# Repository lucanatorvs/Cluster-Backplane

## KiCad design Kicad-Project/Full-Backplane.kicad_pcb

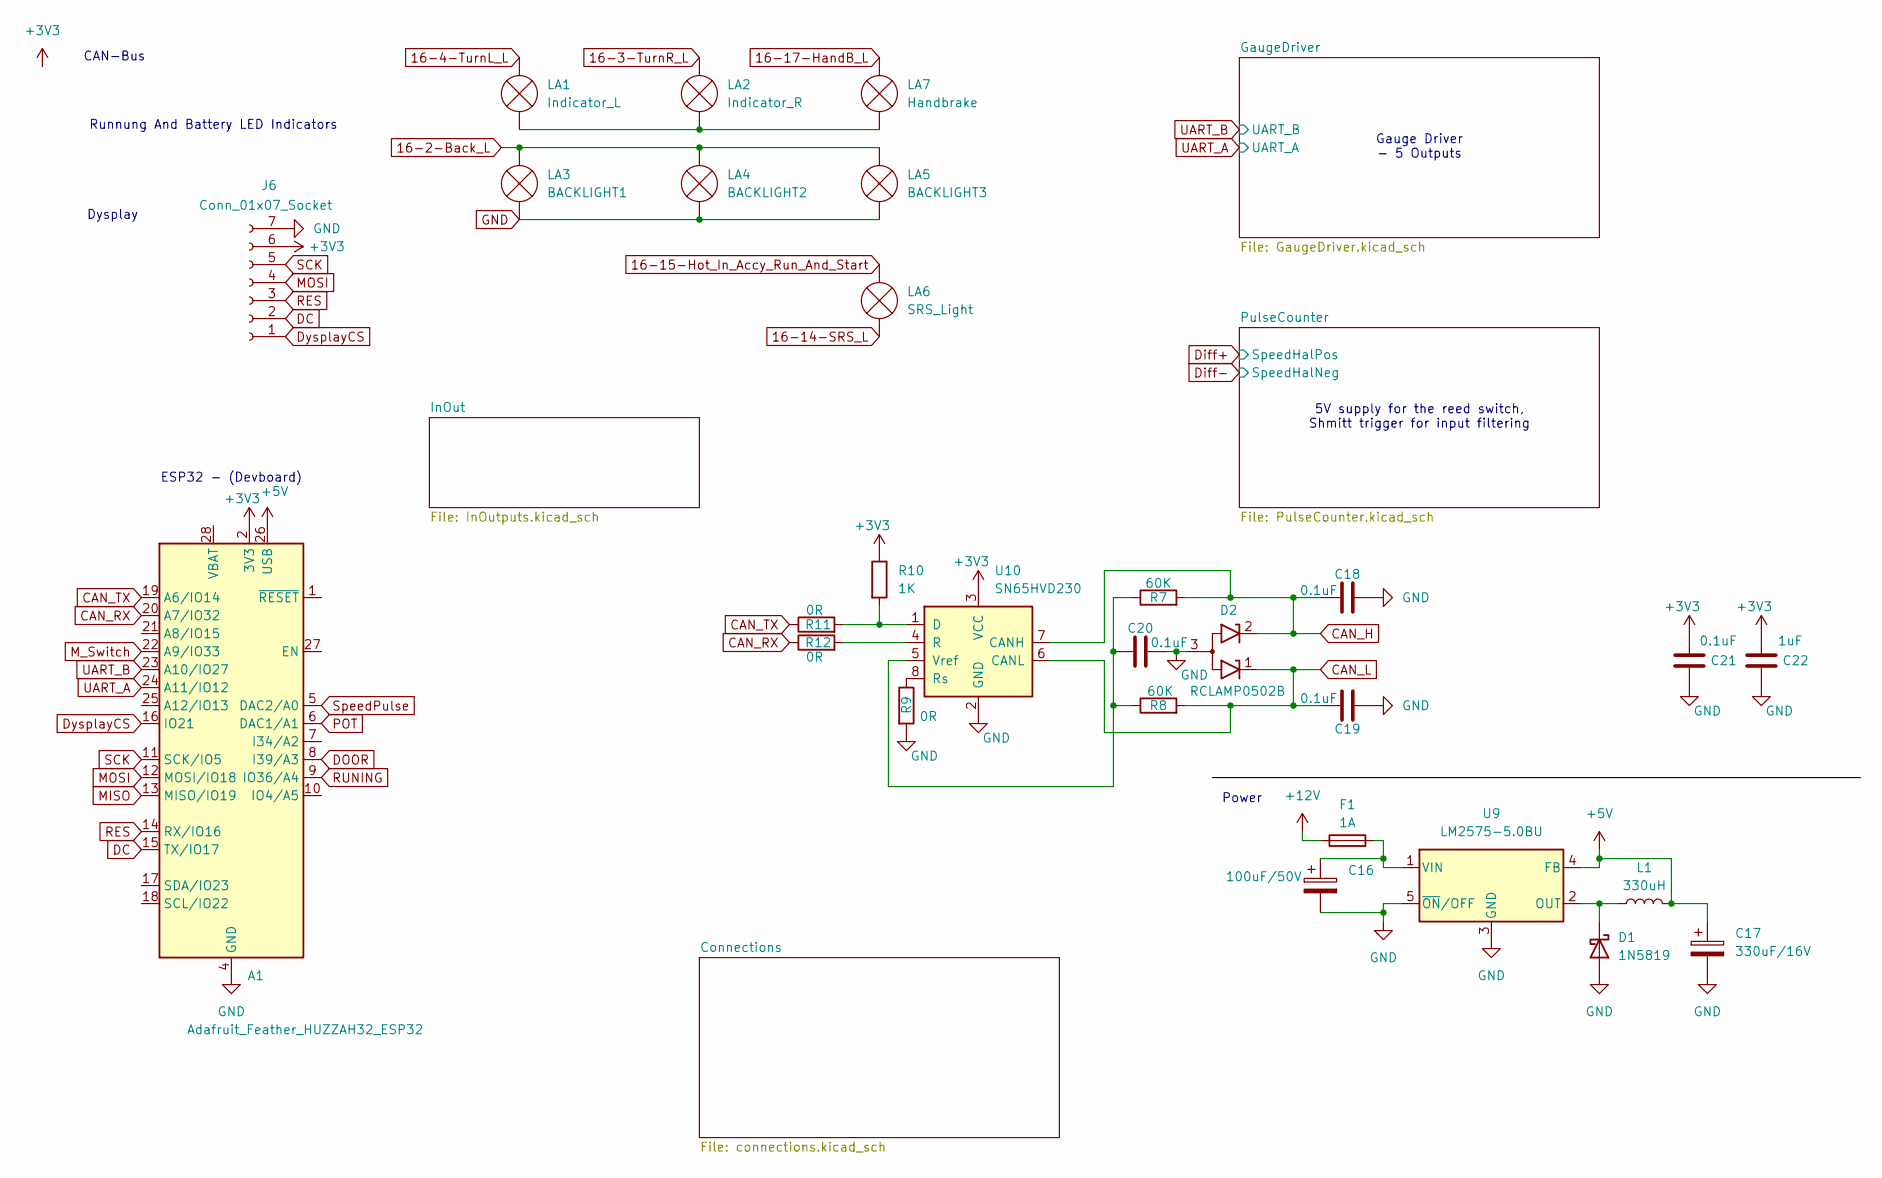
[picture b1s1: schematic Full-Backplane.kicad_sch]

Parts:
A1: Adafruit_Feather_HUZZAH32_ESP32; Adafruit_Feather
C16: 100uF/50V; CP_Radial_D8.0mm_P3.50mm
C17: 330uF/16V; CP_Radial_D8.0mm_P3.50mm
C18, C19, C20, C21: 0.1uF; C_0805_2012Metric_Pad1.18x1.45mm_HandSolder
C22: 1uF; C_0805_2012Metric_Pad1.18x1.45mm_HandSolder
D1: 1N5819; D_DO-41_SOD81_P10.16mm_Horizontal
D2: RCLAMP0502B; SOT-416
F1: 1A; Fuse_0402_1005Metric_Pad0.77x0.64mm_HandSolder
J6: Conn_01x07_Socket; PinHeader_1x07_P2.54mm_Vertical
L1: 330uH; L_Radial_D9.5mm_P5.00mm_Fastron_07HVP
LA1: Indicator_L; Smallight
LA2: Indicator_R; Smallight
LA3: BACKLIGHT1; Biglight
LA4: BACKLIGHT2; Biglight
LA5: BACKLIGHT3; Biglight
LA6: SRS_Light; Smallight
LA7: Handbrake; Smallight
R7, R8: 60K; R_0805_2012Metric_Pad1.20x1.40mm_HandSolder
R9, R11, R12: 0R; R_0805_2012Metric_Pad1.20x1.40mm_HandSolder
R10: 1K; R_0805_2012Metric_Pad1.20x1.40mm_HandSolder
U9: LM2575-5.0BU; TO-263-5_TabPin3
U10: SN65HVD230; SOIC-8_3.9x4.9mm_P1.27mm

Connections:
16-2-Back_L: LA3.2 (+), LA4.2 (+), LA5.2 (+); also elsewhere on the board
16-3-TurnR_L: LA2.2 (+); also elsewhere on the board
16-4-TurnL_L: LA1.2 (+); also elsewhere on the board
16-14-SRS_L: LA6.1 (-); also elsewhere on the board
16-15-Hot_In_Accy_Run_And_Start: LA6.2 (+); also elsewhere on the board
16-17-HandB_L: LA7.2 (+); also elsewhere on the board
+3V3: A1.2 (3V3), C21.1, C22.1, J6.6, R10.1, U10.3 (VCC); also elsewhere on the board
+5V: A1.26 (USB), C17.1, L1.2, U9.4 (FB); also elsewhere on the board
+12V: F1.1
CAN_H: C18.1, D2.2 (K2), R7.2, U10.7 (CANH); also elsewhere on the board
CAN_L: C19.1, D2.1 (K1), R8.2, U10.6 (CANL); also elsewhere on the board
CAN_RX: A1.20 (A7/IO32), R12.1
CAN_TX: A1.19 (A6/IO14), R11.1
DC: A1.15 (TX/IO17), J6.2
DOOR: A1.8 (I39/A3)
DysplayCS: A1.16 (IO21), J6.1
GND: A1.4 (GND), C16.2, C17.2, C18.2, C19.2, C20.2, C21.2, C22.2, D1.2 (A), D2.3 (A), J6.7, LA3.1 (-), LA4.1 (-), LA5.1 (-), R9.2, U9.3 (GND), U9.5 (~ON/OFF), U10.2 (GND); also elsewhere on the board
MISO: A1.13 (MISO/IO19)
MOSI: A1.12 (MOSI/IO18), J6.4
M_Switch: A1.22 (A9/IO33)
unnamed: D1.1 (K), L1.1, U9.2 (OUT)
unnamed: LA1.1 (-), LA2.1 (-), LA7.1 (-)
unnamed: C16.1, F1.2, U9.1 (VIN)
unnamed: R10.2, R11.2, U10.1 (D)
unnamed: R12.2, U10.4 (R)
unnamed: R9.1, U10.8 (Rs)
unnamed: C20.1, R7.1, R8.1, U10.5 (Vref)
POT: A1.6 (DAC1/A1)
RES: A1.14 (RX/IO16), J6.3
RUNING: A1.9 (IO36/A4)
SCK: A1.11 (SCK/IO5), J6.5
SpeedPulse: A1.5 (DAC2/A0); also elsewhere on the board
UART_A: A1.24 (A11/IO12); also elsewhere on the board
UART_B: A1.23 (A10/IO27); also elsewhere on the board

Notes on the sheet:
Gauge Driver - 5 Outputs
5V supply for the reed switch, Shmitt trigger for input filtering
CAN-Bus
Dysplay
Runnung And Battery LED Indicators
Power
ESP32 - (Devboard)

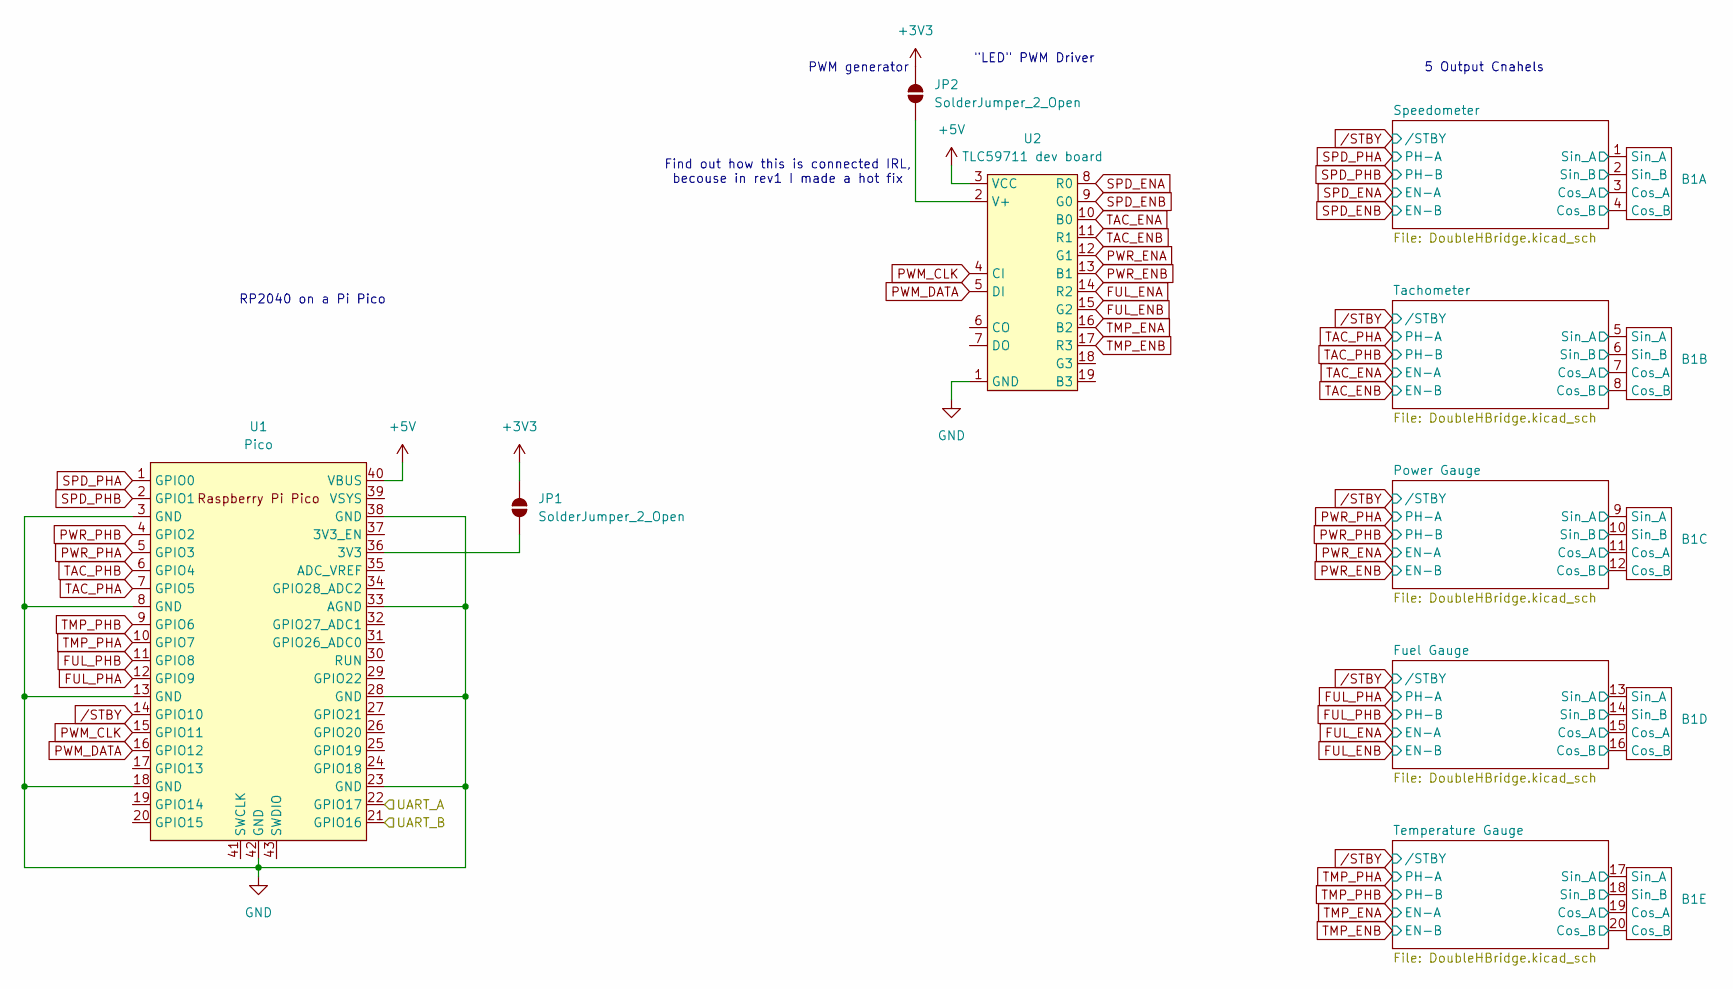
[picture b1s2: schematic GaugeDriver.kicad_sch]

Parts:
B1: Backplane
JP1, JP2: SolderJumper_2_Open; SolderJumper-2_P1.3mm_Open_TrianglePad1.0x1.5mm
U1: Pico; RPi_Pico_SMD_TH
U2: TLC59711 dev board; Adafruit TLC59711

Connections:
+3V3: JP1.2 (B), JP2.2 (B); also elsewhere on the board
+5V: U1.40 (VBUS), U2.3 (VCC); also elsewhere on the board
/GaugeDriver/Fuel Gauge/Cos_A: B1.15 (Cos_A); also elsewhere on the board
/GaugeDriver/Fuel Gauge/Cos_B: B1.16 (Cos_B); also elsewhere on the board
/GaugeDriver/Fuel Gauge/Sin_A: B1.13 (Sin_A); also elsewhere on the board
/GaugeDriver/Fuel Gauge/Sin_B: B1.14 (Sin_B); also elsewhere on the board
/GaugeDriver/Power Gauge/Cos_A: B1.11 (Cos_A); also elsewhere on the board
/GaugeDriver/Power Gauge/Cos_B: B1.12 (Cos_B); also elsewhere on the board
/GaugeDriver/Power Gauge/Sin_A: B1.9 (Sin_A); also elsewhere on the board
/GaugeDriver/Power Gauge/Sin_B: B1.10 (Sin_B); also elsewhere on the board
/GaugeDriver/Speedometer/Cos_A: B1.3 (Cos_A); also elsewhere on the board
/GaugeDriver/Speedometer/Cos_B: B1.4 (Cos_B); also elsewhere on the board
/GaugeDriver/Speedometer/Sin_A: B1.1 (Sin_A); also elsewhere on the board
/GaugeDriver/Speedometer/Sin_B: B1.2 (Sin_B); also elsewhere on the board
/GaugeDriver/Tachometer/Cos_A: B1.7 (Cos_A); also elsewhere on the board
/GaugeDriver/Tachometer/Cos_B: B1.8 (Cos_B); also elsewhere on the board
/GaugeDriver/Tachometer/Sin_A: B1.5 (Sin_A); also elsewhere on the board
/GaugeDriver/Tachometer/Sin_B: B1.6 (Sin_B); also elsewhere on the board
/GaugeDriver/Temperature Gauge/Cos_A: B1.19 (Cos_A); also elsewhere on the board
/GaugeDriver/Temperature Gauge/Cos_B: B1.20 (Cos_B); also elsewhere on the board
/GaugeDriver/Temperature Gauge/Sin_A: B1.17 (Sin_A); also elsewhere on the board
/GaugeDriver/Temperature Gauge/Sin_B: B1.18 (Sin_B); also elsewhere on the board
FUL_ENA: U2.14 (R2); also elsewhere on the board
FUL_ENB: U2.15 (G2); also elsewhere on the board
FUL_PHA: U1.12 (GPIO9); also elsewhere on the board
FUL_PHB: U1.11 (GPIO8); also elsewhere on the board
GND: U1.3 (GND), U1.8 (GND), U1.13 (GND), U1.18 (GND), U1.23 (GND), U1.28 (GND), U1.33 (AGND), U1.38 (GND), U1.42 (GND), U2.1 (GND); also elsewhere on the board
unnamed: JP1.1 (A), U1.36 (3V3)
unnamed: JP2.1 (A), U2.2 (V+)
PWM_CLK: U1.15 (GPIO11), U2.4 (CI)
PWM_DATA: U1.16 (GPIO12), U2.5 (DI)
PWR_ENA: U2.12 (G1); also elsewhere on the board
PWR_ENB: U2.13 (B1); also elsewhere on the board
PWR_PHA: U1.5 (GPIO3); also elsewhere on the board
PWR_PHB: U1.4 (GPIO2); also elsewhere on the board
SPD_ENA: U2.8 (R0); also elsewhere on the board
SPD_ENB: U2.9 (G0); also elsewhere on the board
SPD_PHA: U1.1 (GPIO0); also elsewhere on the board
SPD_PHB: U1.2 (GPIO1); also elsewhere on the board
TAC_ENA: U2.10 (B0); also elsewhere on the board
TAC_ENB: U2.11 (R1); also elsewhere on the board
TAC_PHA: U1.7 (GPIO5); also elsewhere on the board
TAC_PHB: U1.6 (GPIO4); also elsewhere on the board
TMP_ENA: U2.16 (B2); also elsewhere on the board
TMP_ENB: U2.17 (R3); also elsewhere on the board
TMP_PHA: U1.10 (GPIO7); also elsewhere on the board
TMP_PHB: U1.9 (GPIO6); also elsewhere on the board
UART_A: U1.22 (GPIO17); also elsewhere on the board
UART_B: U1.21 (GPIO16); also elsewhere on the board
/STBY: U1.14 (GPIO10); also elsewhere on the board

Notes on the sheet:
RP2040 on a Pi Pico
Find out how this is connected IRL, becouse in rev1 I made a hot fix
5 Output Cnahels
"LED" PWM Driver
PWM generator

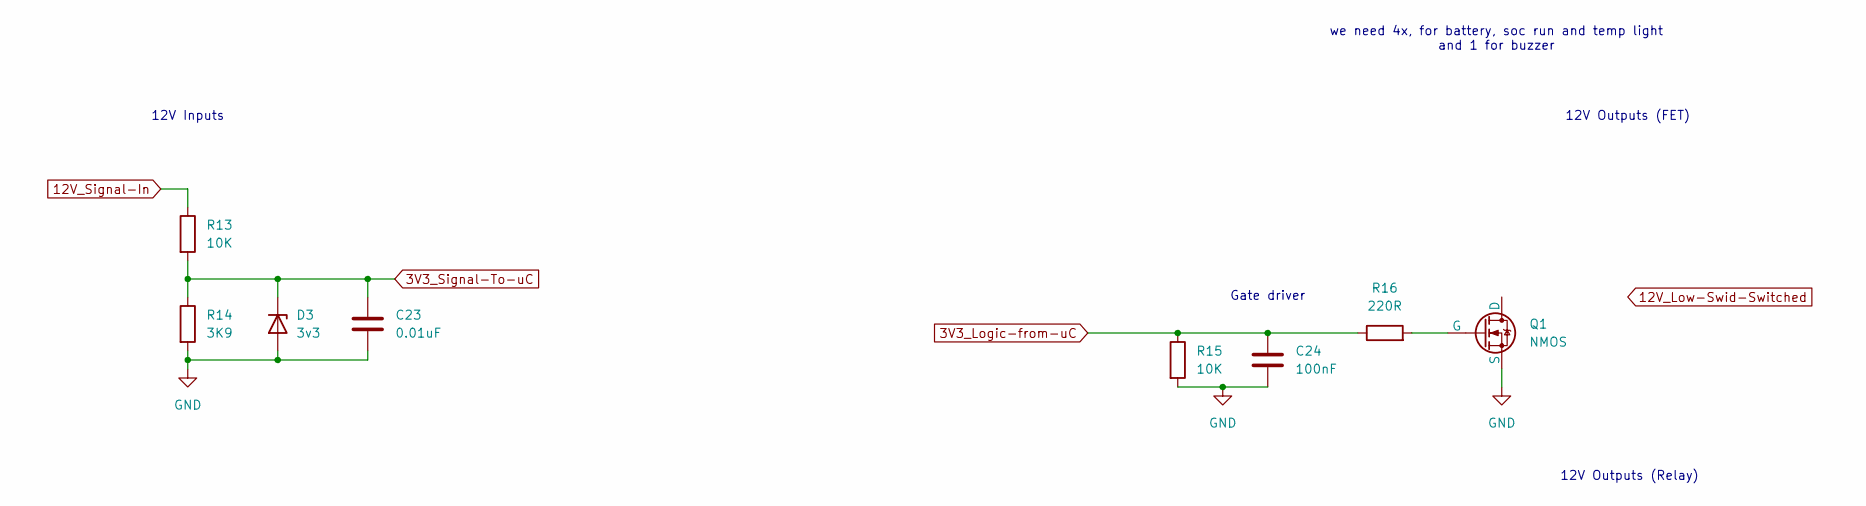
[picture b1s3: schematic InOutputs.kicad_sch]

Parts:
C23: 0.01uF; C_0805_2012Metric_Pad1.18x1.45mm_HandSolder
C24: 100nF
D3: 3v3; D_MiniMELF_Handsoldering
Q1: NMOS; IRFH9714
R13: 10K; R_0805_2012Metric_Pad1.20x1.40mm_HandSolder
R14: 3K9; R_0805_2012Metric_Pad1.20x1.40mm_HandSolder
R15: 10K
R16: 220R

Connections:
3V3_Logic-from-uC: Q1.2 (G), R16.2
3V3_Signal-To-uC: C23.1, D3.1 (K), R13.2, R14.1
12V_Low-Swid-Switched: Q1.1 (D)
12V_Signal-In: R13.1
GND: C23.2, C24.2, D3.2 (A), Q1.3 (S), R14.2, R15.2; also elsewhere on the board
unnamed: C24.1, R15.1, R16.1

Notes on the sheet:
Gate driver
12V Inputs
12V Outputs (Relay)
12V Outputs (FET)
we need 4x, for battery, soc run and temp light and 1 for buzzer

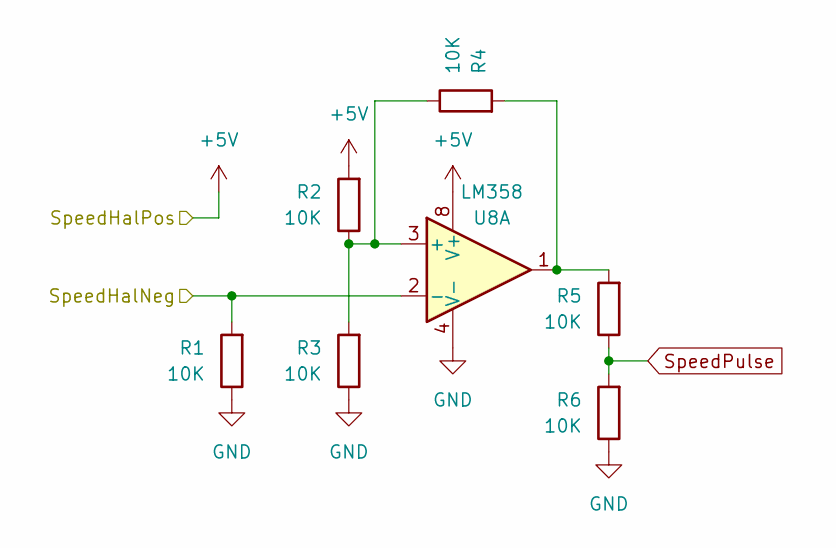
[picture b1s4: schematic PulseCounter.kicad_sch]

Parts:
R1, R2, R3, R4, R5, R6: 10K; R_0805_2012Metric_Pad1.20x1.40mm_HandSolder
U8: LM358; SSOP-8_5.25x5.24mm_P1.27mm

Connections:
Diff+: R2.2, U8.8 (V+); also elsewhere on the board
Diff-: R1.2, U8.2 (-); also elsewhere on the board
GND: R1.1, R3.1, R6.1, U8.4 (V-); also elsewhere on the board
unnamed: R4.2, R5.2, U8.1
unnamed: R2.1, R3.2, R4.1, U8.3 (+)
SpeedPulse: R5.1, R6.2; also elsewhere on the board

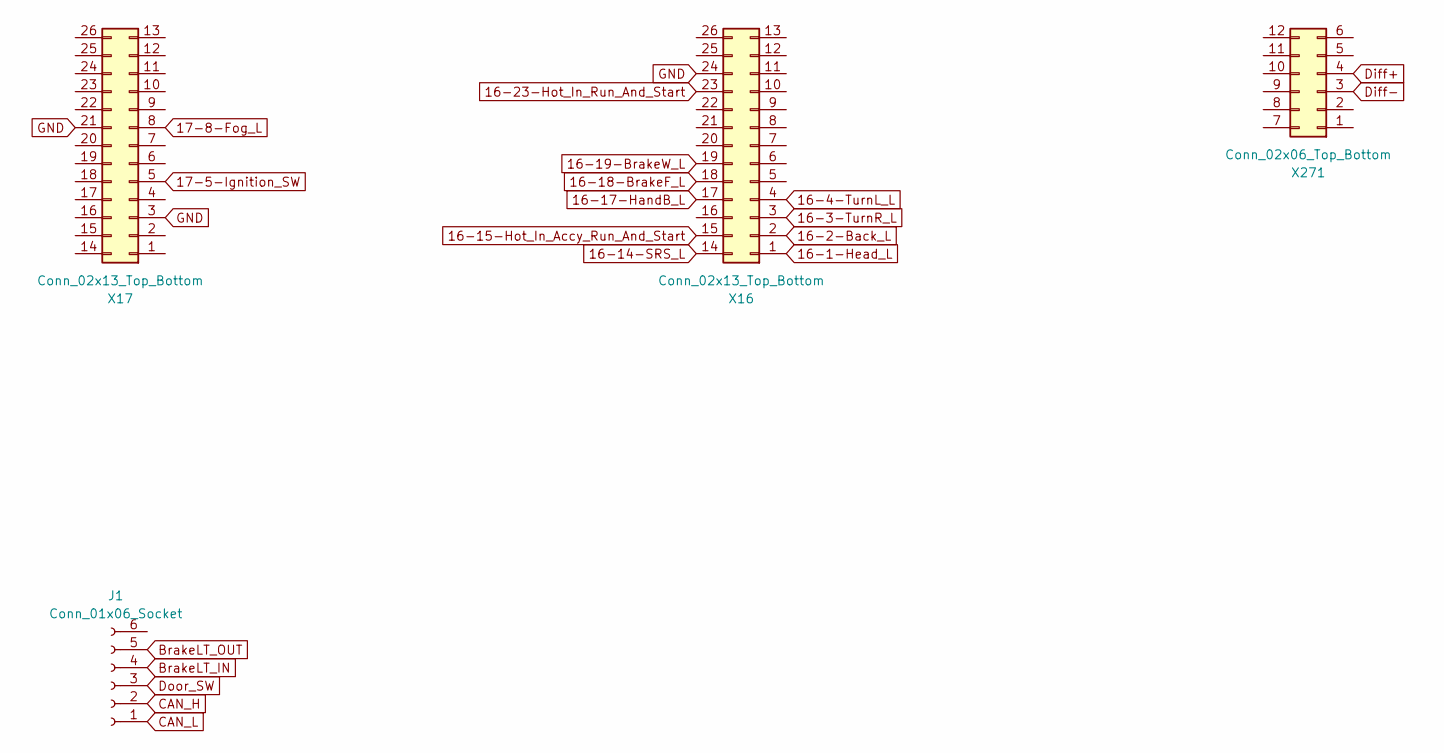
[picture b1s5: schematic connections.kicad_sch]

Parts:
J1: Conn_01x06_Socket; PinHeader_2x03_P2.54mm_Vertical
X16, X17: Conn_02x13_Top_Bottom; PinHeader_2x13_P2.54mm_Vertical
X271: Conn_02x06_Top_Bottom; PinHeader_2x06_P2.54mm_Vertical

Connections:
16-1-Head_L: X16.1
16-2-Back_L: X16.2; also elsewhere on the board
16-3-TurnR_L: X16.3; also elsewhere on the board
16-4-TurnL_L: X16.4; also elsewhere on the board
16-14-SRS_L: X16.14; also elsewhere on the board
16-15-Hot_In_Accy_Run_And_Start: X16.15; also elsewhere on the board
16-17-HandB_L: X16.17; also elsewhere on the board
16-18-BrakeF_L: X16.18
16-19-BrakeW_L: X16.19
16-23-Hot_In_Run_And_Start: X16.23
17-5-Ignition_SW: X17.5
17-8-Fog_L: X17.8
BrakeLT_IN: J1.4
BrakeLT_OUT: J1.5
CAN_H: J1.2; also elsewhere on the board
CAN_L: J1.1; also elsewhere on the board
Diff+: X271.4; also elsewhere on the board
Diff-: X271.3; also elsewhere on the board
Door_SW: J1.3
GND: X16.24, X17.3, X17.21; also elsewhere on the board

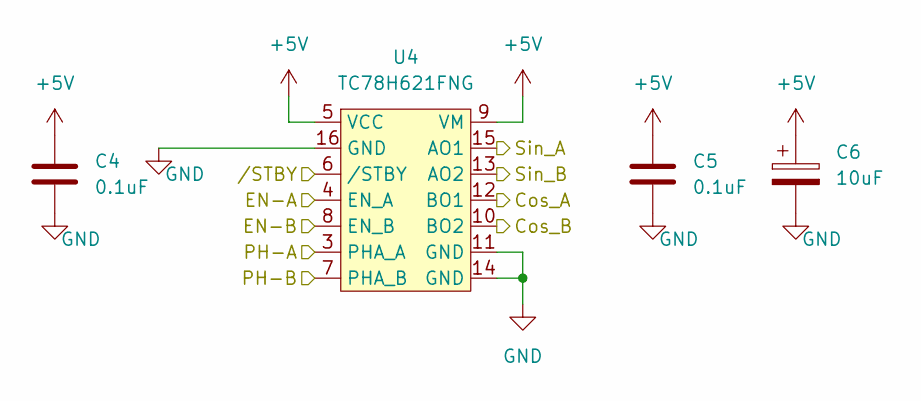
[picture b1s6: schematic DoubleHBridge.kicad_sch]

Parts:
C4, C5: 0.1uF; C_0805_2012Metric
C6: 10uF; CP_Elec_5x5.4
U4: TC78H621FNG; TSSOP-16_4.4x5mm_P0.65mm

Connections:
+5V: C4.1, C5.1, C6.1, U4.5 (VCC), U4.9 (VM); also elsewhere on the board
/GaugeDriver/Speedometer/Cos_A: U4.12 (BO1); also elsewhere on the board
/GaugeDriver/Speedometer/Cos_B: U4.10 (BO2); also elsewhere on the board
/GaugeDriver/Speedometer/Sin_A: U4.15 (AO1); also elsewhere on the board
/GaugeDriver/Speedometer/Sin_B: U4.13 (AO2); also elsewhere on the board
GND: C4.2, C5.2, C6.2, U4.11 (GND), U4.14 (GND), U4.16 (GND); also elsewhere on the board
SPD_ENA: U4.4 (EN_A); also elsewhere on the board
SPD_ENB: U4.8 (EN_B); also elsewhere on the board
SPD_PHA: U4.3 (PHA_A); also elsewhere on the board
SPD_PHB: U4.7 (PHA_B); also elsewhere on the board
/STBY: U4.6 (/STBY); also elsewhere on the board

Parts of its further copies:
C1, C2, C7, C8, C10, C11, C13, C14: 0.1uF; C_0805_2012Metric
C3, C9, C12, C15: 10uF; CP_Elec_5x5.4
U3, U5, U6, U7: TC78H621FNG; TSSOP-16_4.4x5mm_P0.65mm

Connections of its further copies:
+5V: C1.1, C2.1, C3.1, C7.1, C8.1, C9.1, C10.1, C11.1, C12.1, C13.1, C14.1, C15.1, U3.5 (VCC), U3.9 (VM), U5.5 (VCC), U5.9 (VM), U6.5 (VCC), U6.9 (VM), U7.5 (VCC), U7.9 (VM); also elsewhere on the board
/GaugeDriver/Fuel Gauge/Cos_A: U6.12 (BO1); also elsewhere on the board
/GaugeDriver/Fuel Gauge/Cos_B: U6.10 (BO2); also elsewhere on the board
/GaugeDriver/Fuel Gauge/Sin_A: U6.15 (AO1); also elsewhere on the board
/GaugeDriver/Fuel Gauge/Sin_B: U6.13 (AO2); also elsewhere on the board
/GaugeDriver/Power Gauge/Cos_A: U5.12 (BO1); also elsewhere on the board
/GaugeDriver/Power Gauge/Cos_B: U5.10 (BO2); also elsewhere on the board
/GaugeDriver/Power Gauge/Sin_A: U5.15 (AO1); also elsewhere on the board
/GaugeDriver/Power Gauge/Sin_B: U5.13 (AO2); also elsewhere on the board
/GaugeDriver/Tachometer/Cos_A: U3.12 (BO1); also elsewhere on the board
/GaugeDriver/Tachometer/Cos_B: U3.10 (BO2); also elsewhere on the board
/GaugeDriver/Tachometer/Sin_A: U3.15 (AO1); also elsewhere on the board
/GaugeDriver/Tachometer/Sin_B: U3.13 (AO2); also elsewhere on the board
/GaugeDriver/Temperature Gauge/Cos_A: U7.12 (BO1); also elsewhere on the board
/GaugeDriver/Temperature Gauge/Cos_B: U7.10 (BO2); also elsewhere on the board
/GaugeDriver/Temperature Gauge/Sin_A: U7.15 (AO1); also elsewhere on the board
/GaugeDriver/Temperature Gauge/Sin_B: U7.13 (AO2); also elsewhere on the board
FUL_ENA: U6.4 (EN_A); also elsewhere on the board
FUL_ENB: U6.8 (EN_B); also elsewhere on the board
FUL_PHA: U6.3 (PHA_A); also elsewhere on the board
FUL_PHB: U6.7 (PHA_B); also elsewhere on the board
GND: C1.2, C2.2, C3.2, C7.2, C8.2, C9.2, C10.2, C11.2, C12.2, C13.2, C14.2, C15.2, U3.11 (GND), U3.14 (GND), U3.16 (GND), U5.11 (GND), U5.14 (GND), U5.16 (GND), U6.11 (GND), U6.14 (GND), U6.16 (GND), U7.11 (GND), U7.14 (GND), U7.16 (GND); also elsewhere on the board
PWR_ENA: U5.4 (EN_A); also elsewhere on the board
PWR_ENB: U5.8 (EN_B); also elsewhere on the board
PWR_PHA: U5.3 (PHA_A); also elsewhere on the board
PWR_PHB: U5.7 (PHA_B); also elsewhere on the board
TAC_ENA: U3.4 (EN_A); also elsewhere on the board
TAC_ENB: U3.8 (EN_B); also elsewhere on the board
TAC_PHA: U3.3 (PHA_A); also elsewhere on the board
TAC_PHB: U3.7 (PHA_B); also elsewhere on the board
TMP_ENA: U7.4 (EN_A); also elsewhere on the board
TMP_ENB: U7.8 (EN_B); also elsewhere on the board
TMP_PHA: U7.3 (PHA_A); also elsewhere on the board
TMP_PHB: U7.7 (PHA_B); also elsewhere on the board
/STBY: U3.6 (/STBY), U5.6 (/STBY), U6.6 (/STBY), U7.6 (/STBY); also elsewhere on the board

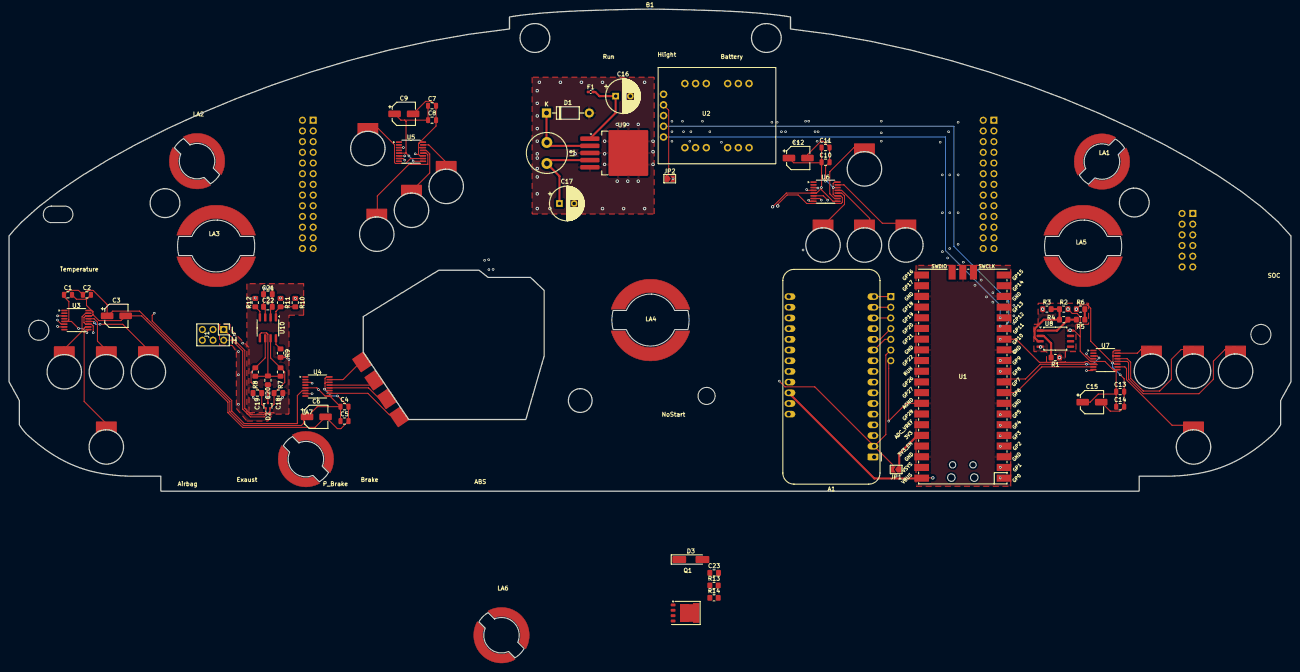
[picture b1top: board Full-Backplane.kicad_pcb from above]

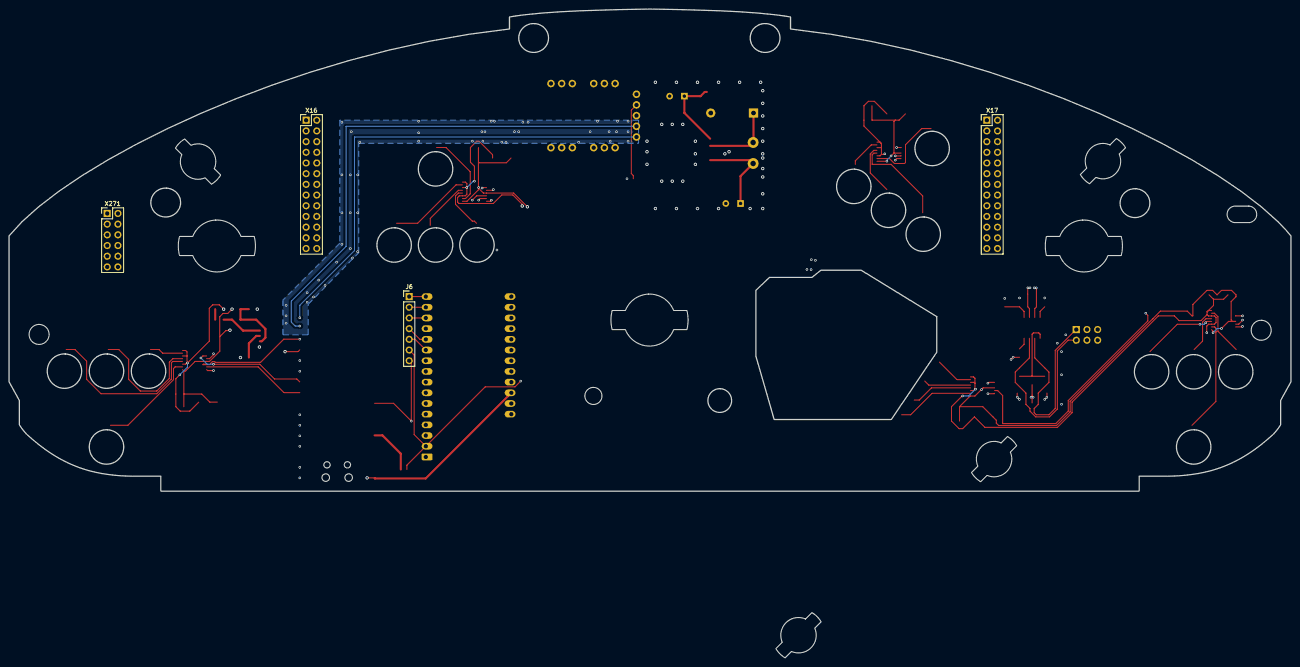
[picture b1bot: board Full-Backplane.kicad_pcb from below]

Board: 4 copper layers, 304.6 x 114.6 mm, 69 parts (4 on the bottom side), 78 nets.

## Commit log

2024-03-17 svg of pcb cutline
2024-03-17 kicad project for backpland pcb
2024-06-15 Reorganize and update project with recent work.
2024-06-15 remove files from having the project open...
